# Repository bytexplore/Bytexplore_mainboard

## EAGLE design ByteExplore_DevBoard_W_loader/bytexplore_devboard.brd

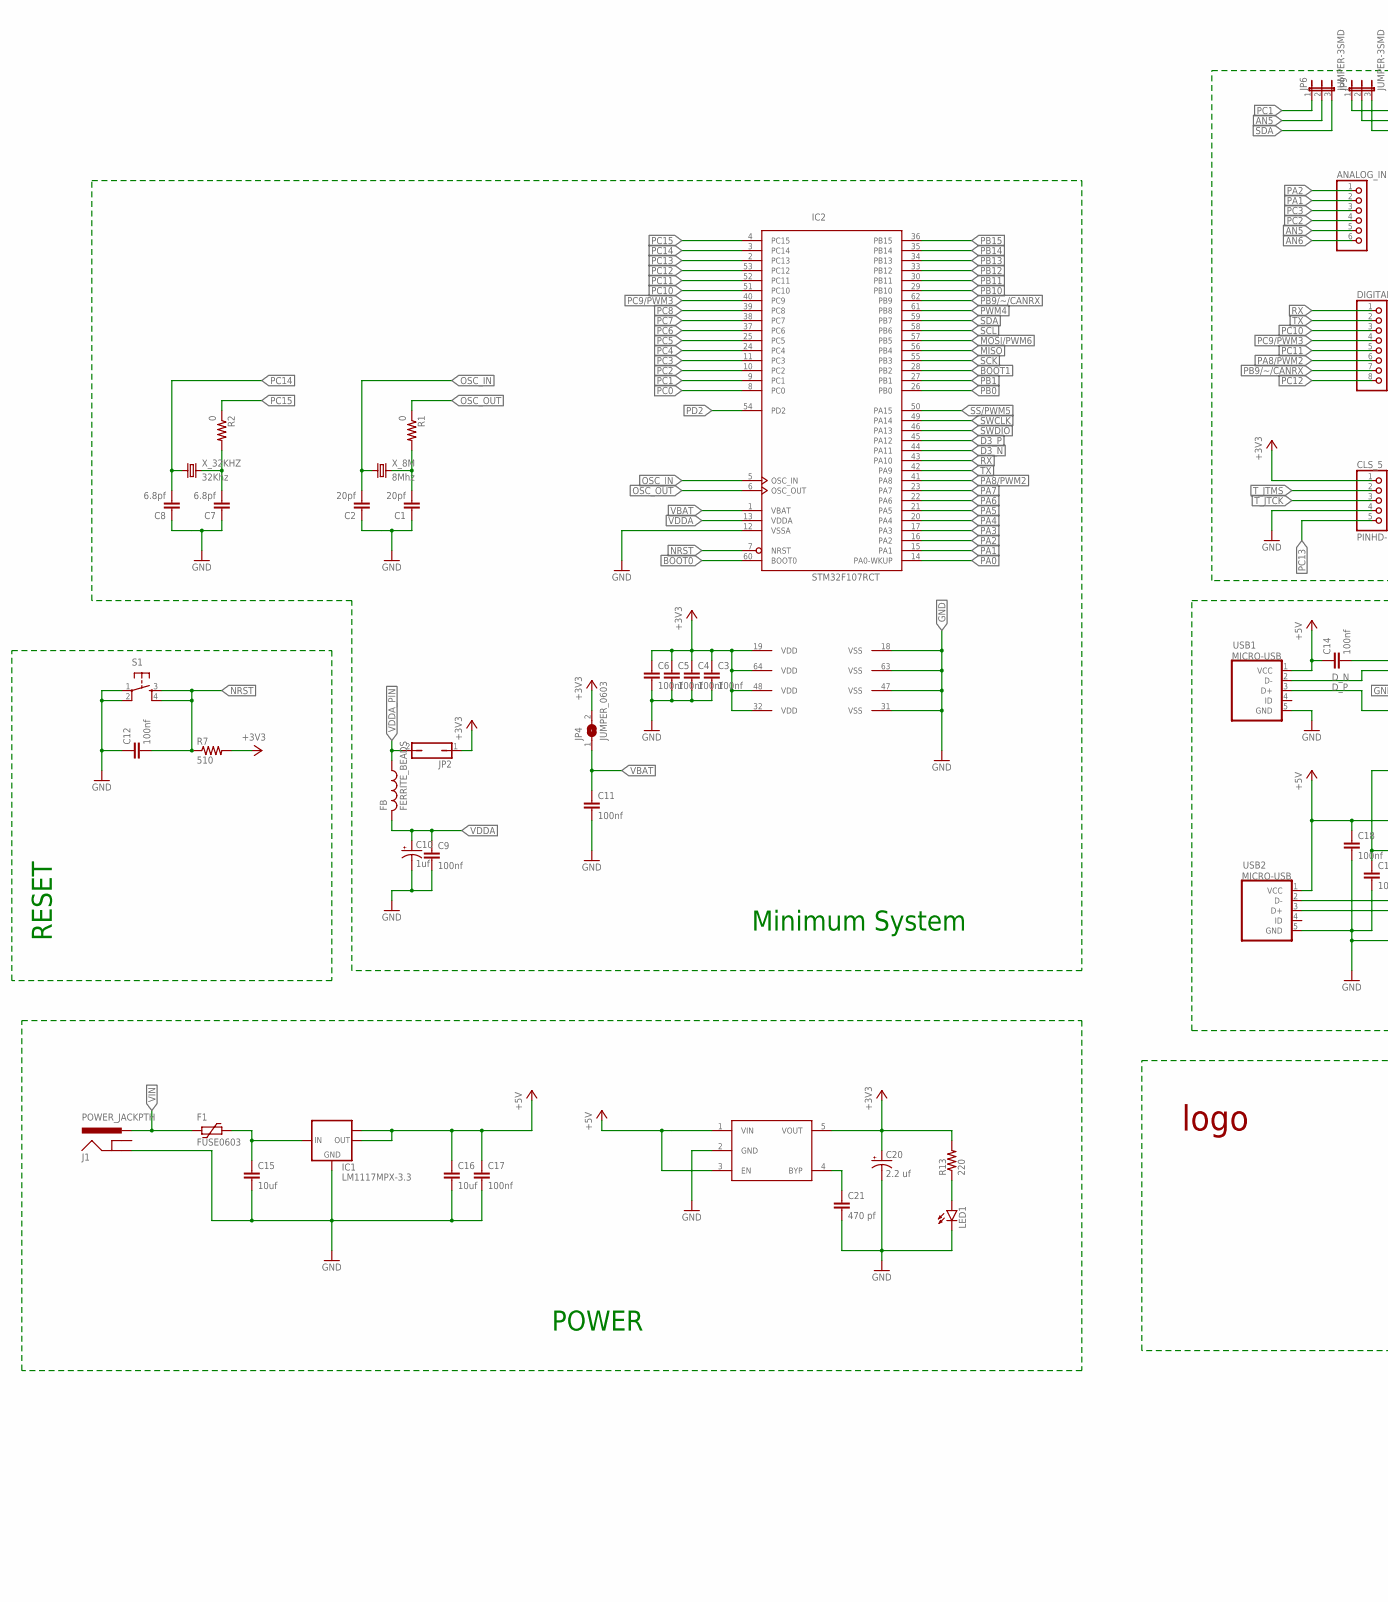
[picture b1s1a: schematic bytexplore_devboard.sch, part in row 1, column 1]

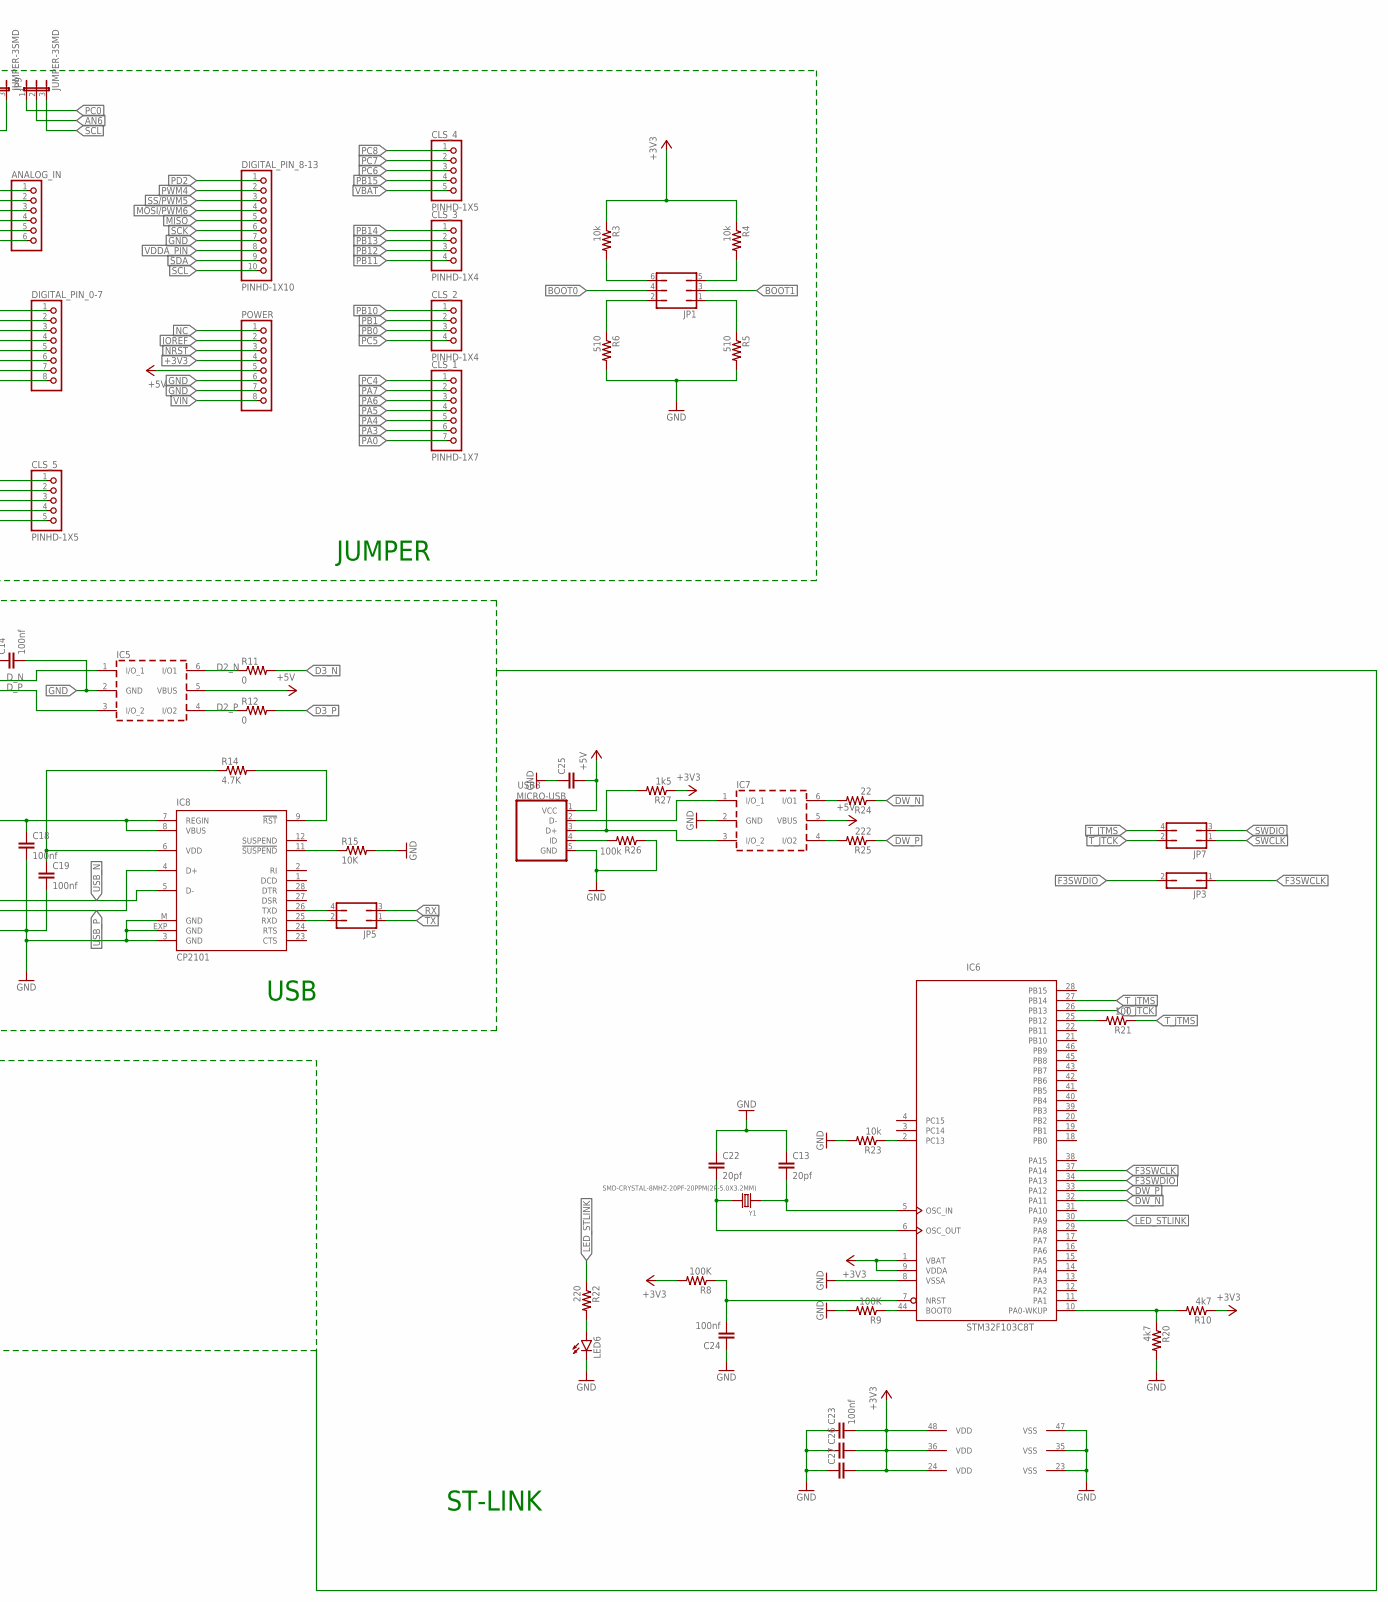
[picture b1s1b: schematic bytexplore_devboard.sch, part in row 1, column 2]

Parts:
ANALOG_IN: PINHD-1X6B; 1X06-BIG
C1, C2: 20pf; C0603K
C3, C4, C5, C6, C9, C11, C12, C14, C18, C19: 100nf; C0603K
C7, C8: 6.8pf; C0603K
C10: 1uf; SMC_B
C13, C22: 20pf; C0603
C15, C16: 10uf; C0603
C17, C23, C24: 100nf; C0603
C20: 2.2 uf; SMC_A
C21: 470 pf; C0603
C25, C26, C27: C-EUC0603; C0603
CLS_1: PINHD-1X7; 1X07-BIG
CLS_2, CLS_3: PINHD-1X4; 1X04-BIG
CLS_4, CLS_5: PINHD-1X5; 1X05-BIG
DIGITAL_PIN_0-7: PINHD-1X8BIG; 1X08-BIG
DIGITAL_PIN_8-13: PINHD-1X10; 1X10-BIG
F1: FUSE0603; R0603
FB: FERRITE_BEADS; R0603
IC1: LM1117MPX-3.3; SOT223
IC2: STM32F107RCT; LQFP64
IC4: MIC5219; SOT-23-5
IC5, IC7: USBLC6-2SC6; SOT-23-6L
IC6: STM32F103C8T; LQFP48
IC8: CP2101; MLP28
J1: POWER_JACKPTH; POWER_JACK_PTH
JP1: JP3Q
JP2, JP3: JP1Q; JP1
JP4: JUMPER_0603; R0603
JP5, JP7: JP2Q
JP6, JP9: JUMPER-3SMD; SJ_3
LED1, LED6: LEDSML0603; SML0603
POWER: PINHD-1X8BIG; 1X08-BIG
R1, R2, R11, R12: 0; R0603
R3, R4, R23: 10k; R0603
R5, R6, R7: 510; R0603
R8, R9: 100K; R0603
R10, R20: 4k7; R0603
R13, R22: 220; R0603
R14: 4.7K; R0603
R15: 10K; R0603
R21: 100; R0603
R24: 22; R0603
R25: 222; R0603
R26: 100k; R0603
R27: 1k5; R0603
S1: TAC_SWITCHPTH; TACTILE-PTH
U$1: LOGO_PME2
USB1, USB2, USB3: MICRO-USB
X_8M: 8Mhz; HC49U70
X_32KHZ: 32Khz; TC26H
Y1: SMD-CRYSTAL-8MHZ-20PF-20PPM(2P-5.0X3.2MM); X2-SMD-5.0X3.2X1.3MM

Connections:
+3V3: C3.1, C4.1, C5.1, C6.1, C20.+, C23.2, C26.2, C27.2, CLS_5.1, IC2.19 (VDD), IC2.32 (VDD), IC2.48 (VDD), IC2.64 (VDD), IC4.5 (VOUT), IC6.1 (VBAT), IC6.9 (VDDA), IC6.24 (VDD), IC6.36 (VDD), IC6.48 (VDD), JP2.1, JP4.2, POWER.4, R3.1, R4.1, R7.2, R8.2, R10.1, R13.2, R27.1
+5V: C14.1, C16.1, C17.1, C18.1, C25.2, IC1.2 (OUT), IC1.TAB (OUT1), IC4.1 (VIN), IC4.3 (EN), IC5.5 (VBUS), IC7.5 (VBUS), IC8.7 (REGIN), IC8.8 (VBUS), POWER.5, USB1.1 (VCC), USB2.1 (VCC), USB3.1 (VCC)
AN5: ANALOG_IN.5, JP6.2
AN6: ANALOG_IN.6, JP9.2
BOOT0: IC2.60 (BOOT0), JP1.4
BOOT1: IC2.28 (PB2), JP1.3
D2_N: IC5.6 (I/O1), R11.1
D2_P: IC5.4 (I/O2), R12.1
D3_N: IC2.44 (PA11), R11.2
D3_P: IC2.45 (PA12), R12.2
DW_N: IC6.32 (PA11), R24.1
DW_P: IC6.33 (PA12), R25.1
D_N: IC5.1 (I/O_1), USB1.2 (D-)
D_P: IC5.3 (I/O_2), USB1.3 (D+)
F3SWCLK: IC6.37 (PA14), JP3.1
F3SWDIO: IC6.34 (PA13), JP3.2
GND: C1.1, C2.1, C3.2, C4.2, C5.2, C6.2, C7.1, C8.1, C9.2, C10.-, C11.2, C12.1, C13.1, C14.2, C15.2, C16.2, C17.2, C18.2, C19.2, C20.-, C21.2, C22.1, C23.1, C24.1, C25.1, C26.1, C27.1, CLS_5.4, DIGITAL_PIN_8-13.7, IC1.1 (GND), IC2.12 (VSSA), IC2.18 (VSS), IC2.31 (VSS), IC2.47 (VSS), IC2.63 (VSS), IC4.2 (GND), IC5.2 (GND), IC6.8 (VSSA), IC6.23 (VSS), IC6.35 (VSS), IC6.47 (VSS), IC7.2 (GND), IC8.3 (GND), IC8.EXP (GND), IC8.M (GND), J1.GND, LED1.C, LED6.C, POWER.6, POWER.7, R5.2, R6.2, R9.2, R15.2, R20.2, R23.2, R26.1, S1.1, S1.2, USB1.5 (GND), USB2.5 (GND), USB3.5 (GND)
IOREF: POWER.2
LED_STLINK: IC6.30 (PA9), R22.1
MISO: DIGITAL_PIN_8-13.5, IC2.56 (PB4)
MOSI/PWM6: DIGITAL_PIN_8-13.4, IC2.57 (PB5)
unnamed: JP1.5, R4.2
unnamed: C1.2, R1.2, X_8M.2
unnamed: JP1.6, R3.2
unnamed: C7.2, R2.2, X_32KHZ.2
unnamed: C19.1, IC8.6 (VDD), R14.1
unnamed: C13.2, IC6.5 (OSC_IN), Y1.1
unnamed: C24.2, IC6.7 (NRST), R8.1
unnamed: C22.2, IC6.6 (OSC_OUT), Y1.2
unnamed: C15.1, F1.1, IC1.3 (IN)
unnamed: IC6.44 (BOOT0), R9.1
unnamed: LED1.A, R13.1
unnamed: IC6.10 (PA0-WKUP), R10.2, R20.1
unnamed: IC6.25 (PB12), R21.2
unnamed: LED6.A, R22.2
unnamed: IC6.2 (PC13), R23.1
unnamed: IC8.9 (!RST), R14.2
unnamed: IC8.11 (!SUSPEND), R15.1
unnamed: IC7.6 (I/O1), R24.2
unnamed: IC8.26 (TXD), JP5.4
unnamed: IC8.25 (RXD), JP5.2
unnamed: IC7.4 (I/O2), R25.2
unnamed: IC7.1 (I/O_1), USB3.2 (D-)
unnamed: JP1.1, R5.1
unnamed: JP1.2, R6.1
unnamed: IC7.3 (I/O_2), R27.2, USB3.3 (D+)
unnamed: R26.2, USB3.4 (ID)
unnamed: C21.1, IC4.4 (BYP)
NC: POWER.1
NRST: C12.2, IC2.7 (NRST), POWER.3, R7.1, S1.3, S1.4
OSC_IN: C2.2, IC2.5 (OSC_IN), X_8M.1
OSC_OUT: IC2.6 (OSC_OUT), R1.1
PA0: CLS_1.7, IC2.14 (PA0-WKUP)
PA1: ANALOG_IN.2, IC2.15 (PA1)
PA2: ANALOG_IN.1, IC2.16 (PA2)
PA3: CLS_1.6, IC2.17 (PA3)
PA4: CLS_1.5, IC2.20 (PA4)
PA5: CLS_1.4, IC2.21 (PA5)
PA6: CLS_1.3, IC2.22 (PA6)
PA7: CLS_1.2, IC2.23 (PA7)
PA8/PWM2: DIGITAL_PIN_0-7.6, IC2.41 (PA8)
PB0: CLS_2.3, IC2.26 (PB0)
PB1: CLS_2.2, IC2.27 (PB1)
PB9/~/CANRX: DIGITAL_PIN_0-7.7, IC2.62 (PB9)
PB10: CLS_2.1, IC2.29 (PB10)
PB11: CLS_3.4, IC2.30 (PB11)
PB12: CLS_3.3, IC2.33 (PB12)
PB13: CLS_3.2, IC2.34 (PB13)
PB14: CLS_3.1, IC2.35 (PB14)
PB15: CLS_4.4, IC2.36 (PB15)
PC0: IC2.8 (PC0), JP9.1
PC1: IC2.9 (PC1), JP6.1
PC2: ANALOG_IN.4, IC2.10 (PC2)
PC3: ANALOG_IN.3, IC2.11 (PC3)
PC4: CLS_1.1, IC2.24 (PC4)
PC5: CLS_2.4, IC2.25 (PC5)
PC6: CLS_4.3, IC2.37 (PC6)
PC7: CLS_4.2, IC2.38 (PC7)
PC8: CLS_4.1, IC2.39 (PC8)
PC9/PWM3: DIGITAL_PIN_0-7.4, IC2.40 (PC9)
PC10: DIGITAL_PIN_0-7.3, IC2.51 (PC10)
PC11: DIGITAL_PIN_0-7.5, IC2.52 (PC11)
PC12: DIGITAL_PIN_0-7.8, IC2.53 (PC12)
PC13: CLS_5.5, IC2.2 (PC13)
PC14: C8.2, IC2.3 (PC14), X_32KHZ.1
PC15: IC2.4 (PC15), R2.1
PD2: DIGITAL_PIN_8-13.1, IC2.54 (PD2)
PWM4: DIGITAL_PIN_8-13.2, IC2.61 (PB8)
RX: DIGITAL_PIN_0-7.1, IC2.43 (PA10), JP5.3
SCK: DIGITAL_PIN_8-13.6, IC2.55 (PB3)
SCL: DIGITAL_PIN_8-13.10, IC2.58 (PB6), JP9.3
SDA: DIGITAL_PIN_8-13.9, IC2.59 (PB7), JP6.3
SS/PWM5: DIGITAL_PIN_8-13.3, IC2.50 (PA15)
SWCLK: IC2.49 (PA14), JP7.1
SWDIO: IC2.46 (PA13), JP7.3
TX: DIGITAL_PIN_0-7.2, IC2.42 (PA9), JP5.1
T_JTCK: CLS_5.3, IC6.26 (PB13), JP7.2
T_JTMS: CLS_5.2, IC6.27 (PB14), JP7.4, R21.1
USB_N: IC8.5 (D-), USB2.2 (D-)
USB_P: IC8.4 (D+), USB2.3 (D+)
VBAT: C11.1, CLS_4.5, IC2.1 (VBAT), JP4.1
VDDA: C9.1, C10.+, FB.2, IC2.13 (VDDA)
VDDA_PIN: DIGITAL_PIN_8-13.8, FB.1, JP2.2
VIN: F1.2, J1.PWR, POWER.8

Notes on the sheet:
Minimum System
RESET
POWER
USB
JUMPER
ST-LINK

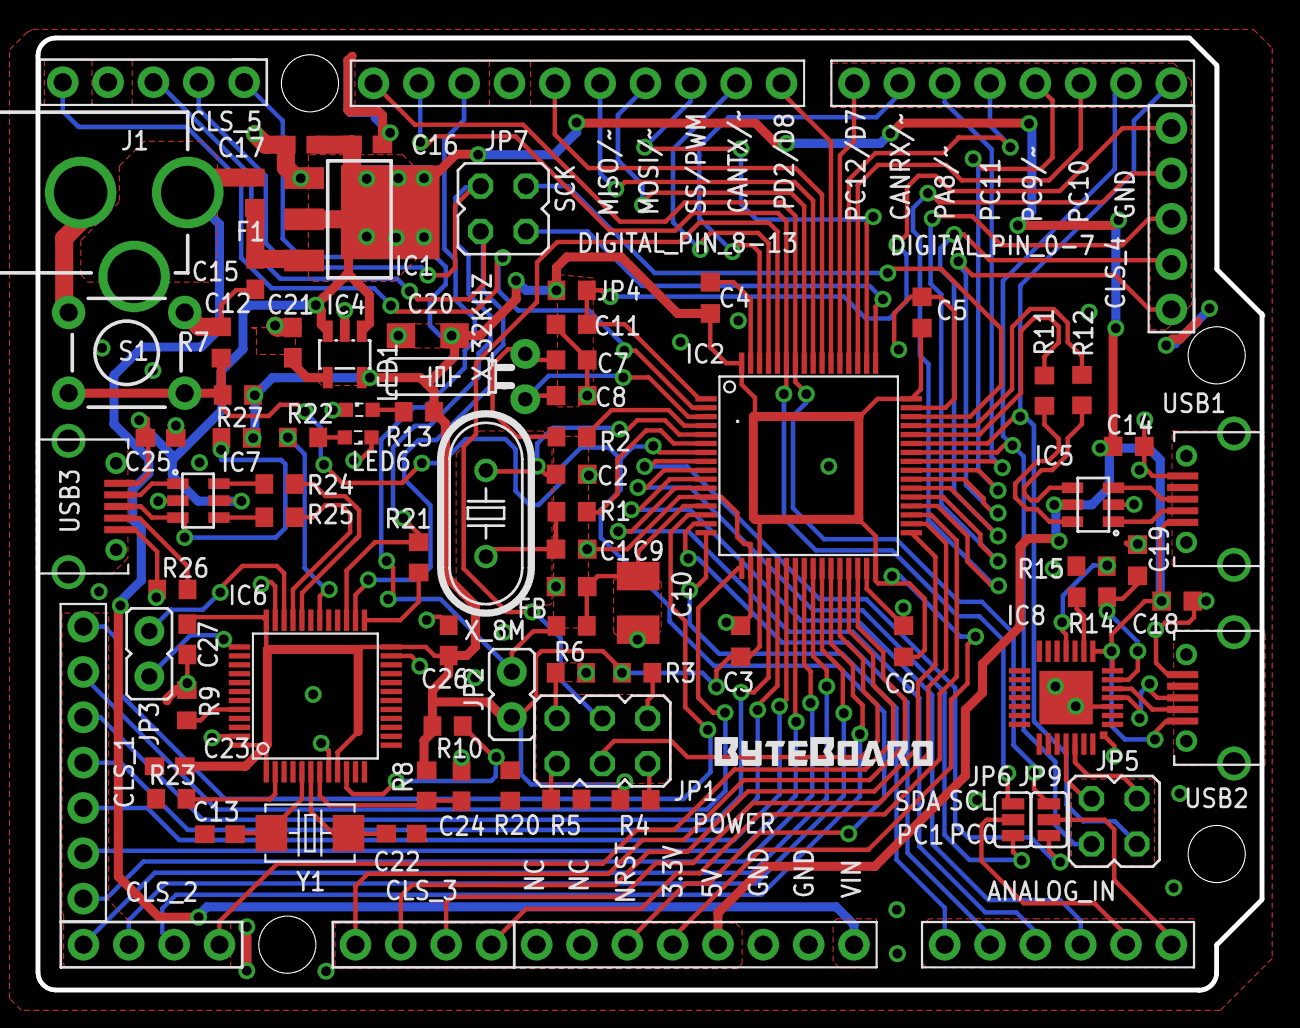
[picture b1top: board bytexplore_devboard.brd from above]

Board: 2 copper layers, 68.6 x 53.3 mm, 87 parts (0 on the bottom side), 102 nets.

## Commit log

2019-05-16 Pcb V.1
2019-07-27 initial commit add a backup file
2019-07-28 initial commit, mainboard V2
2019-08-15 initial commit
    change in power 3V wiring
